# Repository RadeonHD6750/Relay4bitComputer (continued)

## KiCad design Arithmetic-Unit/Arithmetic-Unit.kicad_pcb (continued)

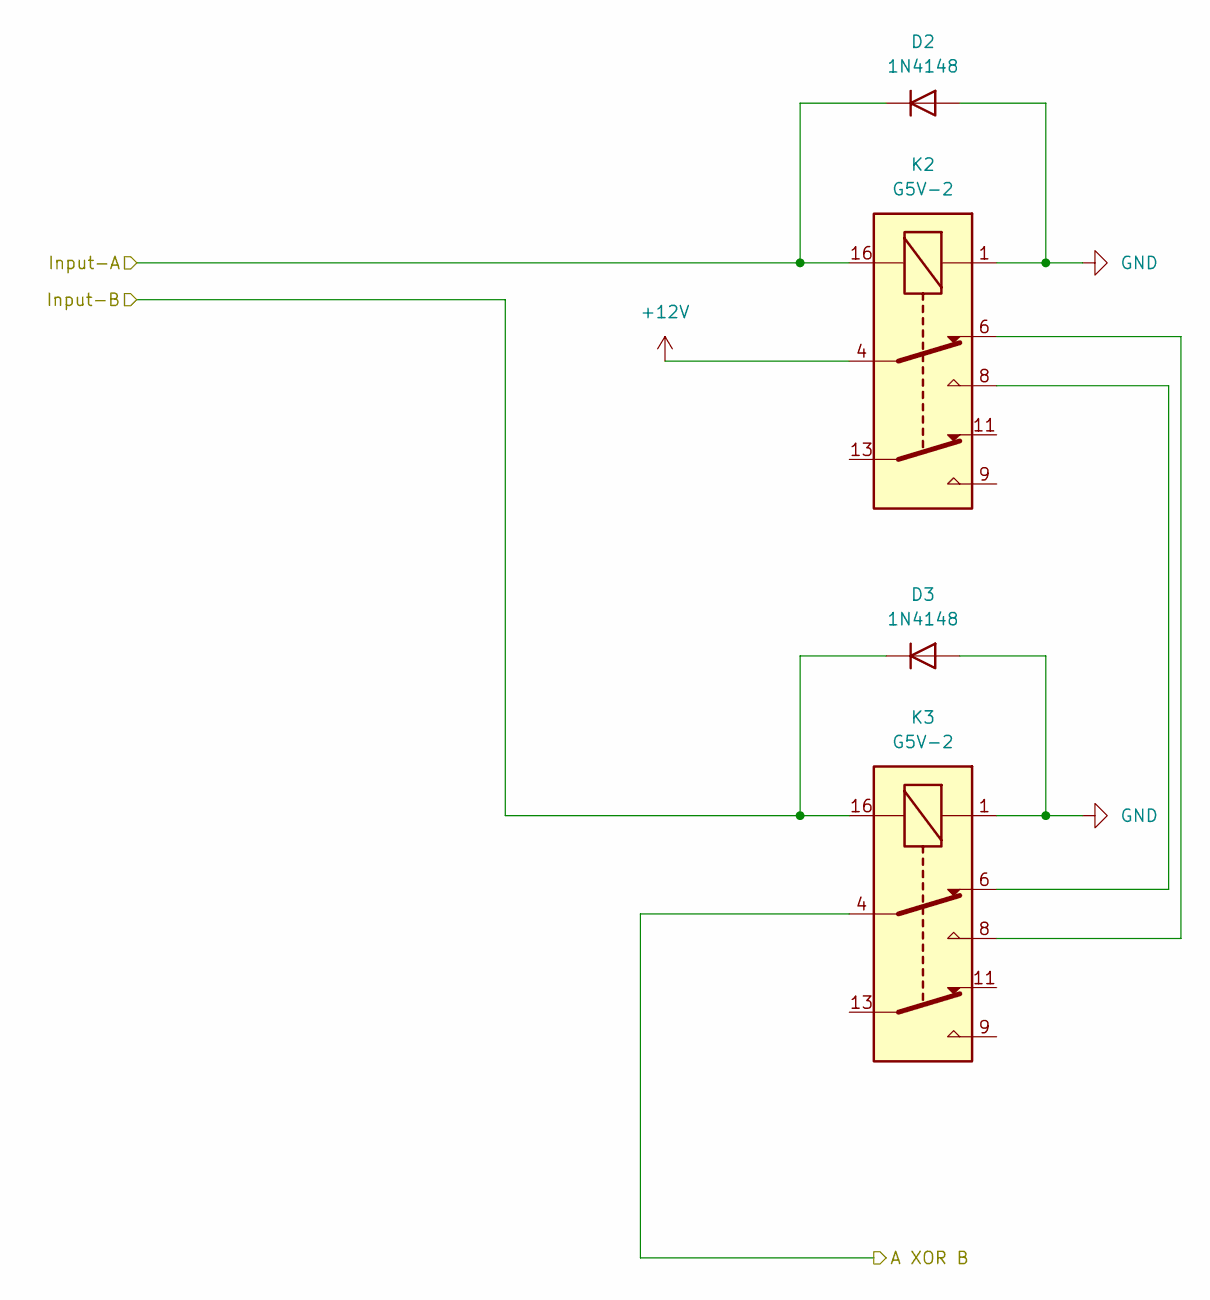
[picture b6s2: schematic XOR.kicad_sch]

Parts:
D2, D3: 1N4148; D_DO-35_SOD27_P7.62mm_Horizontal
K2, K3: G5V-2; Relay_DPDT_Omron_G5V-2

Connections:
+12V: K2.4; also elsewhere on the board
/XOR/A XOR B: K3.4; also elsewhere on the board
/XOR/Input-A: D2.1 (K), K2.16; also elsewhere on the board
/XOR/Input-B: D3.1 (K), K3.16; also elsewhere on the board
GND: D2.2 (A), D3.2 (A), K2.1, K3.1; also elsewhere on the board
unnamed: K2.6, K3.8
unnamed: K2.8, K3.6

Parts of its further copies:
D4, D5, D6, D7, D8, D9: 1N4148; D_DO-35_SOD27_P7.62mm_Horizontal
K4, K5, K6, K7, K8, K9: G5V-2; Relay_DPDT_Omron_G5V-2

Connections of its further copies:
+12V: K4.4, K6.4, K8.4; also elsewhere on the board
/XOR1/A XOR B: K5.4; also elsewhere on the board
/XOR1/Input-B: D5.1 (K), K5.16; also elsewhere on the board
/XOR2/A XOR B: K7.4; also elsewhere on the board
/XOR2/Input-B: D7.1 (K), K7.16; also elsewhere on the board
/XOR3/A XOR B: K9.4; also elsewhere on the board
/XOR3/Input-B: D9.1 (K), K9.16; also elsewhere on the board
/XOR/Input-A: D4.1 (K), D6.1 (K), D8.1 (K), K4.16, K6.16, K8.16; also elsewhere on the board
GND: D4.2 (A), D5.2 (A), D6.2 (A), D7.2 (A), D8.2 (A), D9.2 (A), K4.1, K5.1, K6.1, K7.1, K8.1, K9.1; also elsewhere on the board
unnamed: K4.6, K5.8
unnamed: K4.8, K5.6
unnamed: K6.6, K7.8
unnamed: K6.8, K7.6
unnamed: K8.6, K9.8
unnamed: K8.8, K9.6

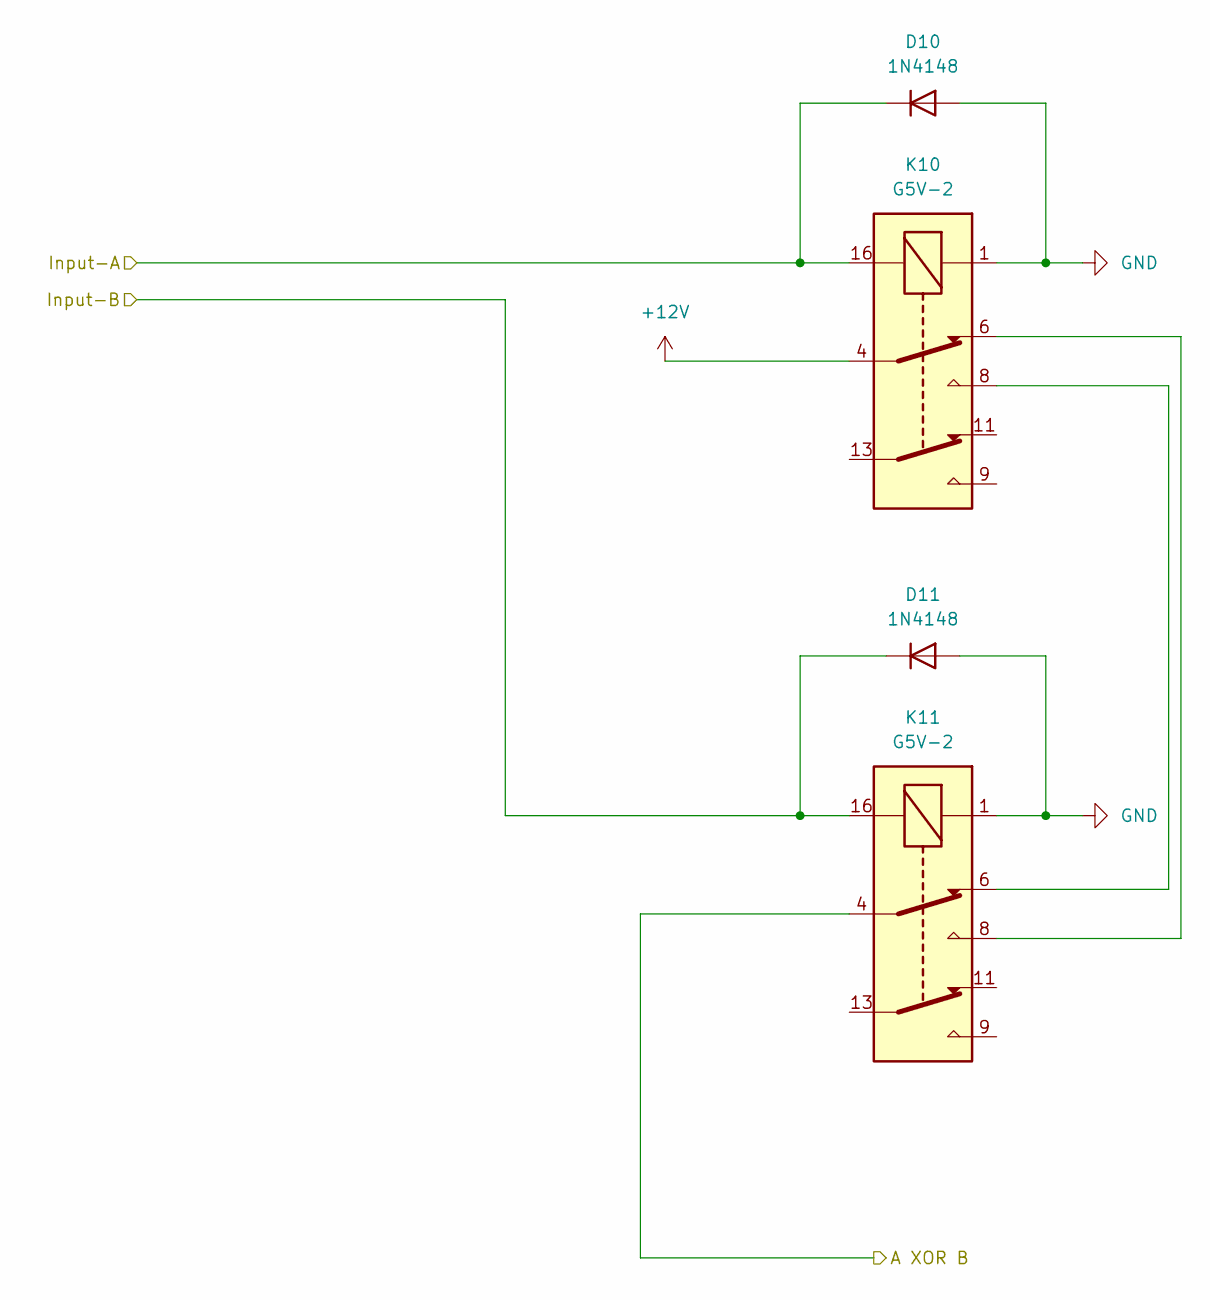
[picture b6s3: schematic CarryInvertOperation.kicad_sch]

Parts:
D10, D11: 1N4148; D_DO-35_SOD27_P7.62mm_Horizontal
K10, K11: G5V-2; Relay_DPDT_Omron_G5V-2

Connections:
+12V: K10.4; also elsewhere on the board
/CarryInvertOperation/A XOR B: K11.4; also elsewhere on the board
/CarryInvertOperation/Input-A: D10.1 (K), K10.16; also elsewhere on the board
/CarryInvertOperation/Input-B: D11.1 (K), K11.16; also elsewhere on the board
GND: D10.2 (A), D11.2 (A), K10.1, K11.1; also elsewhere on the board
unnamed: K10.6, K11.8
unnamed: K10.8, K11.6

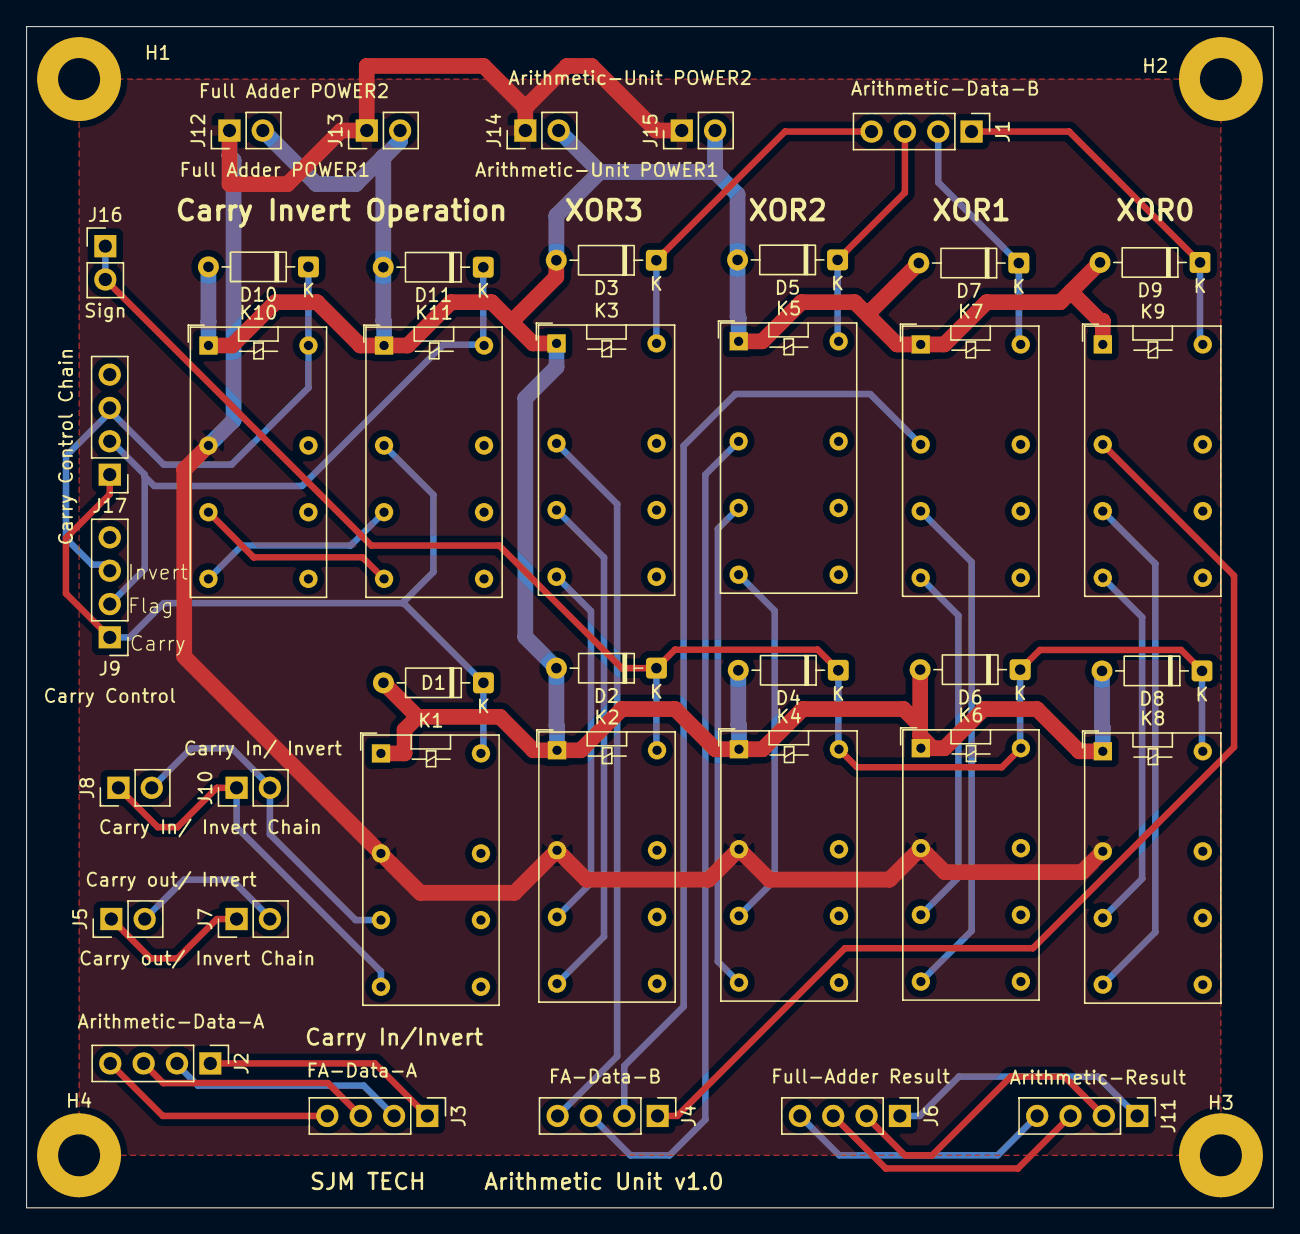
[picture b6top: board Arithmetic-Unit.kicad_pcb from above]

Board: 2 copper layers, 95.0 x 90.0 mm, 43 parts (0 on the bottom side), 36 nets.

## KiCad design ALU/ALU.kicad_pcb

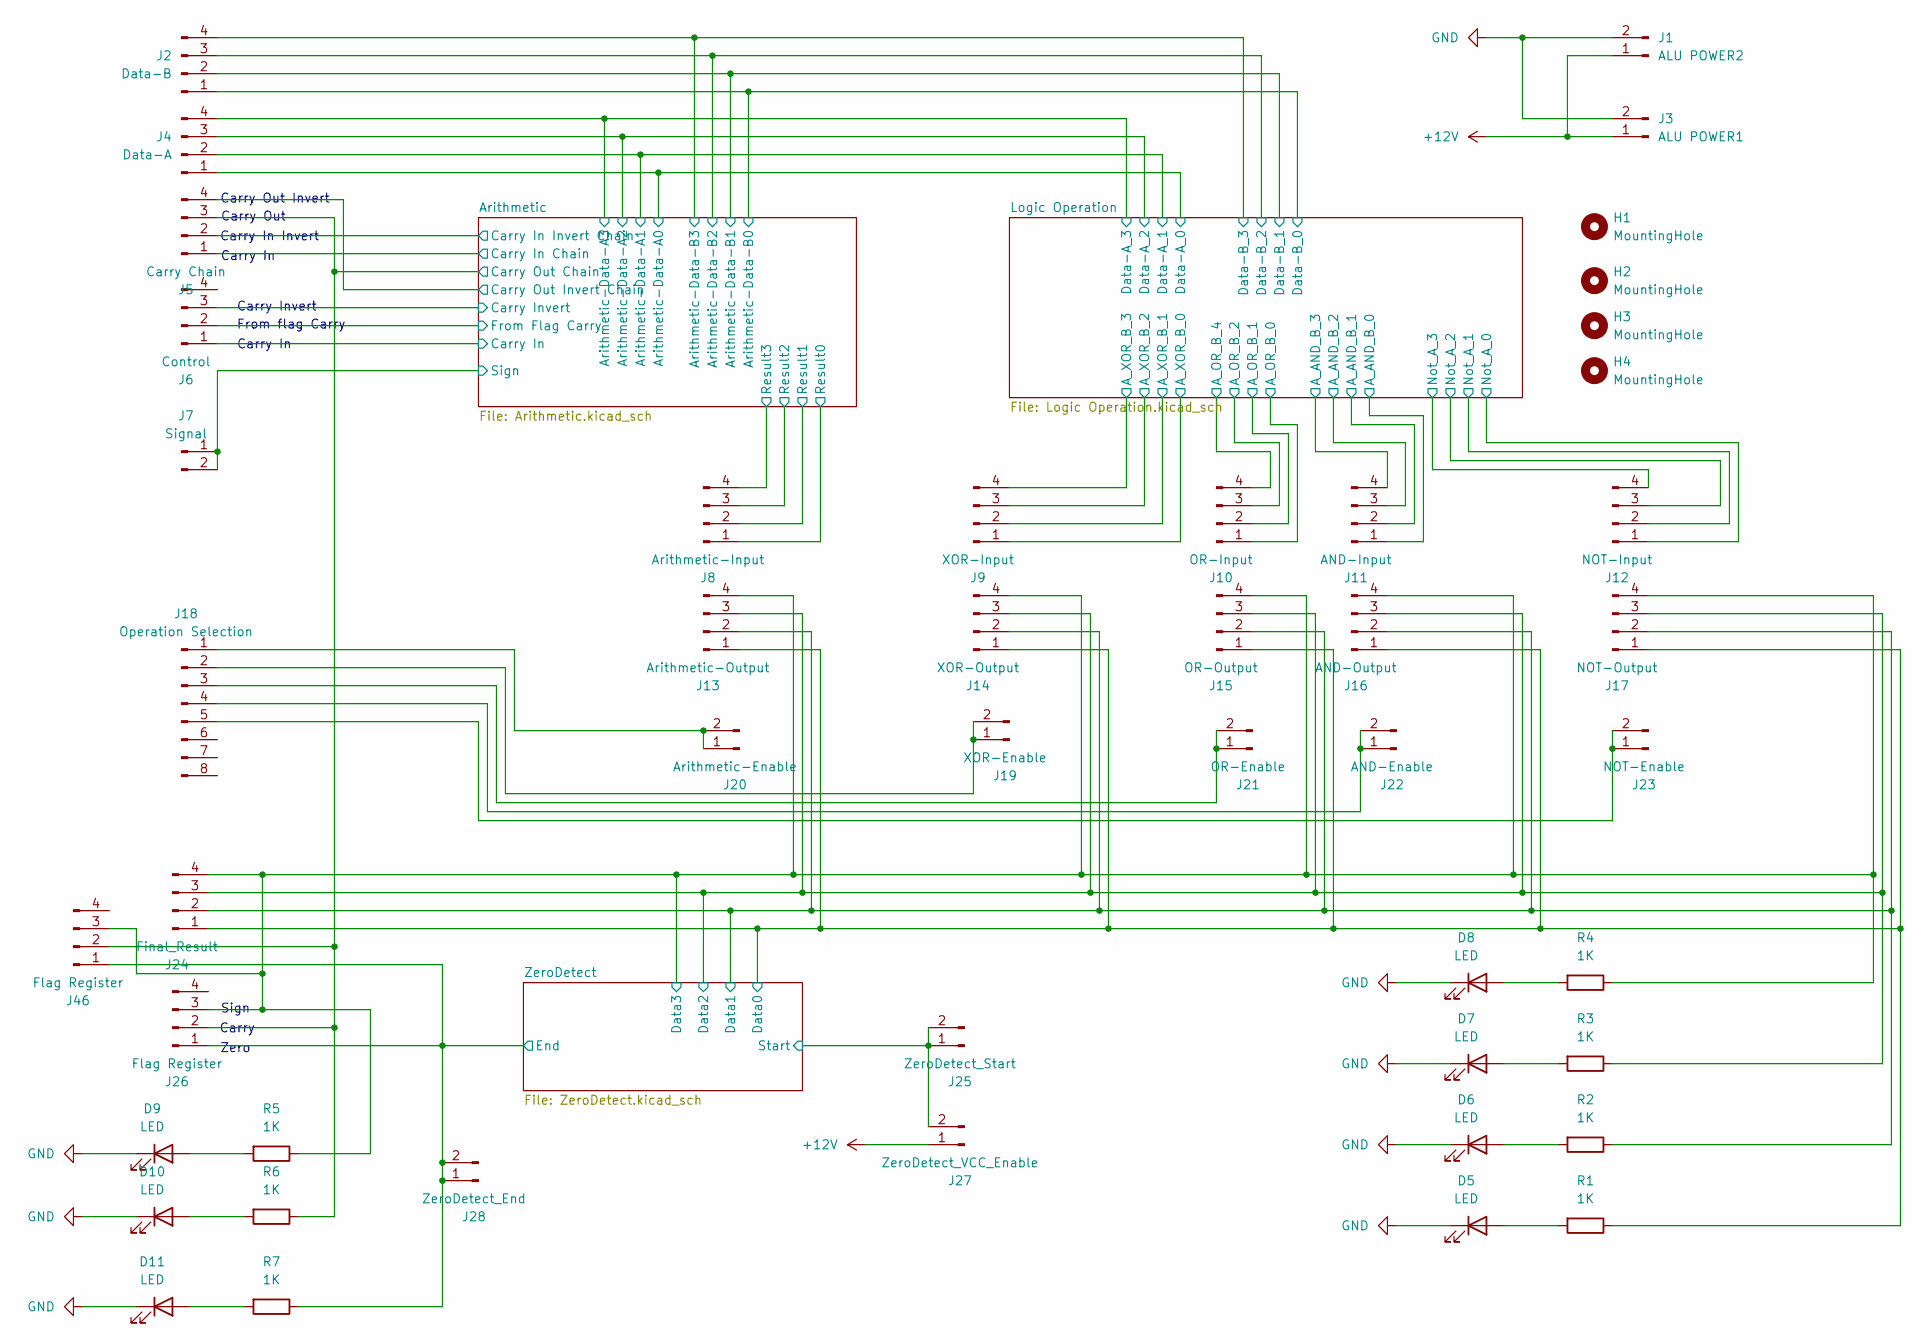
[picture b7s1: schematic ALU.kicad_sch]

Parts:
D5, D6, D7, D8, D9, D10, D11: LED; LED_D5.0mm
H1, H2, H3, H4: MountingHole; MountingHole_3.2mm_M3_Pad
J1: ALU POWER2; PinHeader_1x02_P2.54mm_Vertical
J2: Data-B; PinHeader_1x04_P2.54mm_Vertical
J3: ALU POWER1; PinHeader_1x02_P2.54mm_Vertical
J4: Data-A; PinHeader_1x04_P2.54mm_Vertical
J5: Carry Chain; PinHeader_1x04_P2.54mm_Vertical
J6: Control; PinHeader_1x04_P2.54mm_Vertical
J7: Signal; PinHeader_1x02_P2.54mm_Vertical
J8: Arithmetic-Input; PinHeader_1x04_P2.54mm_Vertical
J9: XOR-Input; PinHeader_1x04_P2.54mm_Vertical
J10: OR-Input; PinHeader_1x04_P2.54mm_Vertical
J11: AND-Input; PinHeader_1x04_P2.54mm_Vertical
J12: NOT-Input; PinHeader_1x04_P2.54mm_Vertical
J13: Arithmetic-Output; PinHeader_1x04_P2.54mm_Vertical
J14: XOR-Output; PinHeader_1x04_P2.54mm_Vertical
J15: OR-Output; PinHeader_1x04_P2.54mm_Vertical
J16: AND-Output; PinHeader_1x04_P2.54mm_Vertical
J17: NOT-Output; PinHeader_1x04_P2.54mm_Vertical
J18: Operation Selection; PinHeader_1x08_P2.54mm_Vertical
J19: XOR-Enable; PinHeader_1x02_P2.54mm_Vertical
J20: Arithmetic-Enable; PinHeader_1x02_P2.54mm_Vertical
J21: OR-Enable; PinHeader_1x02_P2.54mm_Vertical
J22: AND-Enable; PinHeader_1x02_P2.54mm_Vertical
J23: NOT-Enable; PinHeader_1x02_P2.54mm_Vertical
J24: Final_Result; PinHeader_1x04_P2.54mm_Vertical
J25: ZeroDetect_Start; PinHeader_1x02_P2.54mm_Vertical
J26, J46: Flag Register; PinHeader_1x04_P2.54mm_Vertical
J27: ZeroDetect_VCC_Enable; PinHeader_1x02_P2.54mm_Vertical
J28: ZeroDetect_End; PinHeader_1x02_P2.54mm_Vertical
R1, R2, R3, R4, R5, R6, R7: 1K; R_Axial_DIN0207_L6.3mm_D2.5mm_P10.16mm_Horizontal

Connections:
+12V: J1.1, J3.1, J27.1; also elsewhere on the board
/Arithmetic/Arithmetic-Data-A0: J4.1; also elsewhere on the board
/Arithmetic/Arithmetic-Data-A1: J4.2; also elsewhere on the board
/Arithmetic/Arithmetic-Data-A2: J4.3; also elsewhere on the board
/Arithmetic/Arithmetic-Data-A3: J4.4; also elsewhere on the board
/Arithmetic/Arithmetic-Data-B0: J2.1; also elsewhere on the board
/Arithmetic/Arithmetic-Data-B1: J2.2; also elsewhere on the board
/Arithmetic/Arithmetic-Data-B2: J2.3; also elsewhere on the board
/Arithmetic/Arithmetic-Data-B3: J2.4; also elsewhere on the board
/Arithmetic/Carry In: J6.1; also elsewhere on the board
/Arithmetic/Carry In Chain: J5.1; also elsewhere on the board
/Arithmetic/Carry In Invert Chain: J5.2; also elsewhere on the board
/Arithmetic/Carry Invert: J6.3; also elsewhere on the board
/Arithmetic/Carry Out Chain: J5.3, J26.2, J46.2, R6.1; also elsewhere on the board
/Arithmetic/Carry Out Invert Chain: J5.4; also elsewhere on the board
/Arithmetic/From Flag Carry: J6.2; also elsewhere on the board
/Arithmetic/Result0: J8.1; also elsewhere on the board
/Arithmetic/Result1: J8.2; also elsewhere on the board
/Arithmetic/Result2: J8.3; also elsewhere on the board
/Arithmetic/Result3: J8.4; also elsewhere on the board
/Arithmetic/Sign: J7.1, J7.2; also elsewhere on the board
/Logic Operation/A_AND_B_0: J11.1; also elsewhere on the board
/Logic Operation/A_AND_B_1: J11.2; also elsewhere on the board
/Logic Operation/A_AND_B_2: J11.3; also elsewhere on the board
/Logic Operation/A_AND_B_3: J11.4; also elsewhere on the board
/Logic Operation/A_OR_B_0: J10.1; also elsewhere on the board
/Logic Operation/A_OR_B_1: J10.2; also elsewhere on the board
/Logic Operation/A_OR_B_2: J10.3; also elsewhere on the board
/Logic Operation/A_OR_B_4: J10.4; also elsewhere on the board
/Logic Operation/A_XOR_B_0: J9.1; also elsewhere on the board
/Logic Operation/A_XOR_B_1: J9.2; also elsewhere on the board
/Logic Operation/A_XOR_B_2: J9.3; also elsewhere on the board
/Logic Operation/A_XOR_B_3: J9.4; also elsewhere on the board
/Logic Operation/Not_A_0: J12.1; also elsewhere on the board
/Logic Operation/Not_A_1: J12.2; also elsewhere on the board
/Logic Operation/Not_A_2: J12.3; also elsewhere on the board
/Logic Operation/Not_A_3: J12.4; also elsewhere on the board
/ZeroDetect/Data0: J13.1, J14.1, J15.1, J16.1, J17.1, J24.1, R1.1; also elsewhere on the board
/ZeroDetect/Data1: J13.2, J14.2, J15.2, J16.2, J17.2, J24.2, R2.1; also elsewhere on the board
/ZeroDetect/Data2: J13.3, J14.3, J15.3, J16.3, J17.3, J24.3, R3.1; also elsewhere on the board
/ZeroDetect/Data3: J13.4, J14.4, J15.4, J16.4, J17.4, J24.4, J26.3, J46.3, R4.1, R5.1; also elsewhere on the board
/ZeroDetect/End: J26.1, J28.1, J28.2, J46.1, R7.1; also elsewhere on the board
/ZeroDetect/Start: J25.1, J25.2, J27.2; also elsewhere on the board
GND: D5.1 (K), D6.1 (K), D7.1 (K), D8.1 (K), D9.1 (K), D10.1 (K), D11.1 (K), J1.2, J3.2; also elsewhere on the board
unnamed: D5.2 (A), R1.2
unnamed: D6.2 (A), R2.2
unnamed: D7.2 (A), R3.2
unnamed: D8.2 (A), R4.2
unnamed: D9.2 (A), R5.2
unnamed: D10.2 (A), R6.2
unnamed: D11.2 (A), R7.2
unnamed: J18.1, J20.1, J20.2
unnamed: J18.2, J19.1, J19.2
unnamed: J18.3, J21.1, J21.2
unnamed: J18.4, J22.1, J22.2
unnamed: J18.5, J23.1, J23.2

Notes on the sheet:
Carry In
Sign
Carry
From flag Carry
Carry In Invert
Zero
Carry Out
Carry Out Invert
Carry Invert

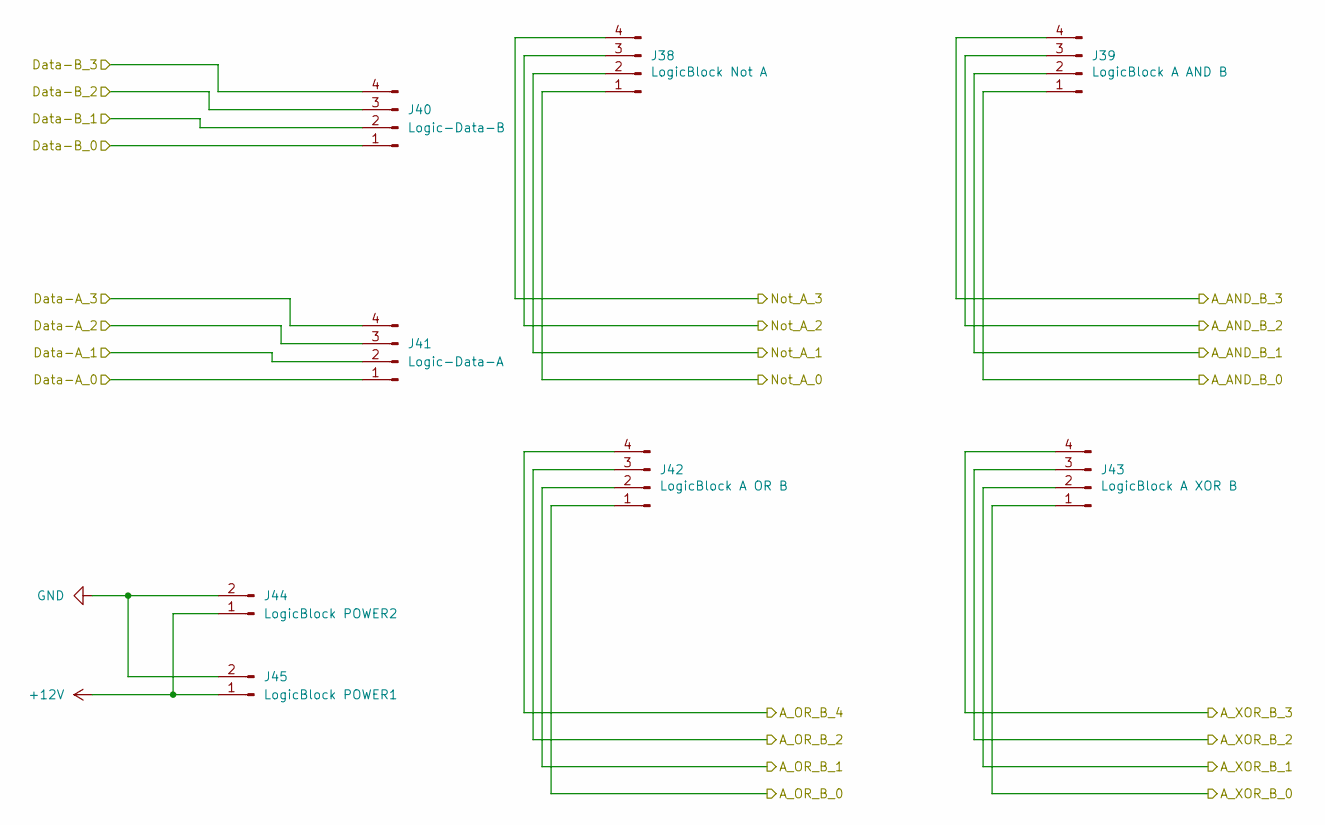
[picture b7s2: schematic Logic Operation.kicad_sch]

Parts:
J38: LogicBlock Not A; PinHeader_1x04_P2.54mm_Vertical
J39: LogicBlock A AND B; PinHeader_1x04_P2.54mm_Vertical
J40: Logic-Data-B; PinHeader_1x04_P2.54mm_Vertical
J41: Logic-Data-A; PinHeader_1x04_P2.54mm_Vertical
J42: LogicBlock A OR B; PinHeader_1x04_P2.54mm_Vertical
J43: LogicBlock A XOR B; PinHeader_1x04_P2.54mm_Vertical
J44: LogicBlock POWER2; PinHeader_1x02_P2.54mm_Vertical
J45: LogicBlock POWER1; PinHeader_1x02_P2.54mm_Vertical

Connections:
+12V: J44.1, J45.1; also elsewhere on the board
/Arithmetic/Arithmetic-Data-A0: J41.1; also elsewhere on the board
/Arithmetic/Arithmetic-Data-A1: J41.2; also elsewhere on the board
/Arithmetic/Arithmetic-Data-A2: J41.3; also elsewhere on the board
/Arithmetic/Arithmetic-Data-A3: J41.4; also elsewhere on the board
/Arithmetic/Arithmetic-Data-B0: J40.1; also elsewhere on the board
/Arithmetic/Arithmetic-Data-B1: J40.2; also elsewhere on the board
/Arithmetic/Arithmetic-Data-B2: J40.3; also elsewhere on the board
/Arithmetic/Arithmetic-Data-B3: J40.4; also elsewhere on the board
/Logic Operation/A_AND_B_0: J39.1; also elsewhere on the board
/Logic Operation/A_AND_B_1: J39.2; also elsewhere on the board
/Logic Operation/A_AND_B_2: J39.3; also elsewhere on the board
/Logic Operation/A_AND_B_3: J39.4; also elsewhere on the board
/Logic Operation/A_OR_B_0: J42.1; also elsewhere on the board
/Logic Operation/A_OR_B_1: J42.2; also elsewhere on the board
/Logic Operation/A_OR_B_2: J42.3; also elsewhere on the board
/Logic Operation/A_OR_B_4: J42.4; also elsewhere on the board
/Logic Operation/A_XOR_B_0: J43.1; also elsewhere on the board
/Logic Operation/A_XOR_B_1: J43.2; also elsewhere on the board
/Logic Operation/A_XOR_B_2: J43.3; also elsewhere on the board
/Logic Operation/A_XOR_B_3: J43.4; also elsewhere on the board
/Logic Operation/Not_A_0: J38.1; also elsewhere on the board
/Logic Operation/Not_A_1: J38.2; also elsewhere on the board
/Logic Operation/Not_A_2: J38.3; also elsewhere on the board
/Logic Operation/Not_A_3: J38.4; also elsewhere on the board
GND: J44.2, J45.2; also elsewhere on the board

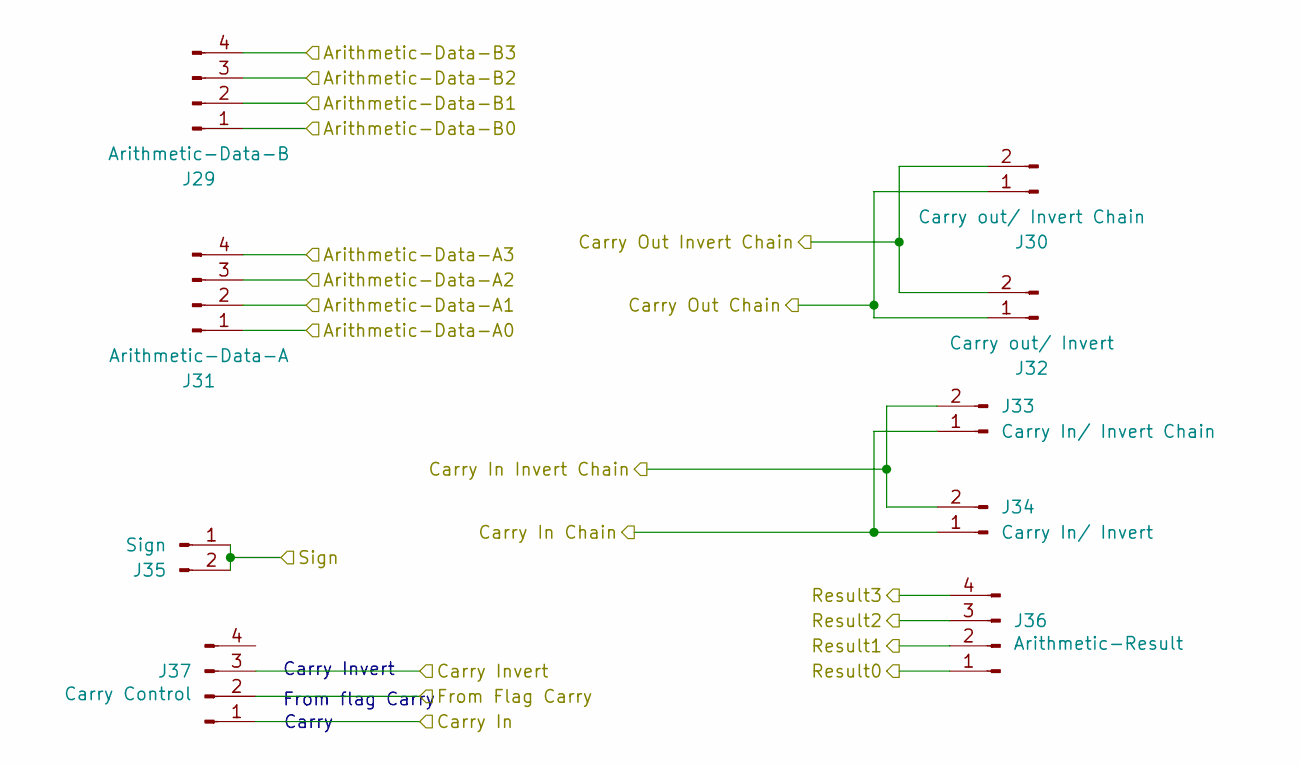
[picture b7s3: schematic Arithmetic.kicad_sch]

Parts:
J29: Arithmetic-Data-B; PinHeader_1x04_P2.54mm_Vertical
J30: Carry out/ Invert Chain; PinHeader_1x02_P2.54mm_Vertical
J31: Arithmetic-Data-A; PinHeader_1x04_P2.54mm_Vertical
J32: Carry out/ Invert; PinHeader_1x02_P2.54mm_Vertical
J33: Carry In/ Invert Chain; PinHeader_1x02_P2.54mm_Vertical
J34: Carry In/ Invert; PinHeader_1x02_P2.54mm_Vertical
J35: Sign; PinHeader_1x02_P2.54mm_Vertical
J36: Arithmetic-Result; PinHeader_1x04_P2.54mm_Vertical
J37: Carry Control; PinHeader_1x04_P2.54mm_Vertical

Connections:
/Arithmetic/Arithmetic-Data-A0: J31.1; also elsewhere on the board
/Arithmetic/Arithmetic-Data-A1: J31.2; also elsewhere on the board
/Arithmetic/Arithmetic-Data-A2: J31.3; also elsewhere on the board
/Arithmetic/Arithmetic-Data-A3: J31.4; also elsewhere on the board
/Arithmetic/Arithmetic-Data-B0: J29.1; also elsewhere on the board
/Arithmetic/Arithmetic-Data-B1: J29.2; also elsewhere on the board
/Arithmetic/Arithmetic-Data-B2: J29.3; also elsewhere on the board
/Arithmetic/Arithmetic-Data-B3: J29.4; also elsewhere on the board
/Arithmetic/Carry In: J37.1; also elsewhere on the board
/Arithmetic/Carry In Chain: J33.1, J34.1; also elsewhere on the board
/Arithmetic/Carry In Invert Chain: J33.2, J34.2; also elsewhere on the board
/Arithmetic/Carry Invert: J37.3; also elsewhere on the board
/Arithmetic/Carry Out Chain: J30.1, J32.1; also elsewhere on the board
/Arithmetic/Carry Out Invert Chain: J30.2, J32.2; also elsewhere on the board
/Arithmetic/From Flag Carry: J37.2; also elsewhere on the board
/Arithmetic/Result0: J36.1; also elsewhere on the board
/Arithmetic/Result1: J36.2; also elsewhere on the board
/Arithmetic/Result2: J36.3; also elsewhere on the board
/Arithmetic/Result3: J36.4; also elsewhere on the board
/Arithmetic/Sign: J35.1, J35.2; also elsewhere on the board

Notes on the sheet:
Carry
From flag Carry
Carry Invert

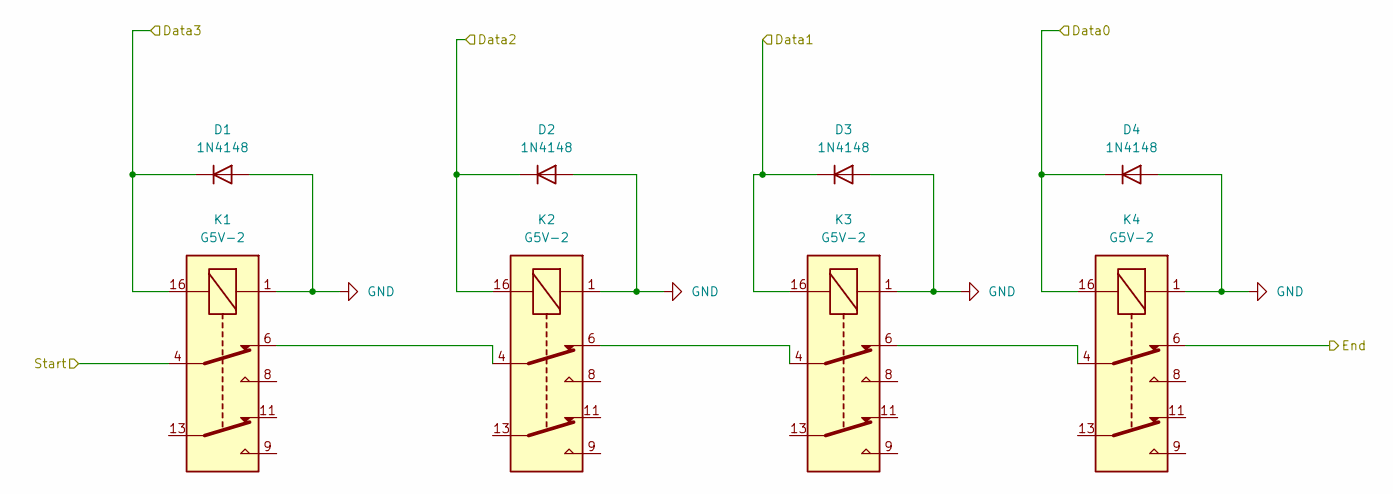
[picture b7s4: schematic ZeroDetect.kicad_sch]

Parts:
D1, D2, D3, D4: 1N4148; D_DO-35_SOD27_P7.62mm_Horizontal
K1, K2, K3, K4: G5V-2; Relay_DPDT_Omron_G5V-2

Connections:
/ZeroDetect/Data0: D4.1 (K), K4.16; also elsewhere on the board
/ZeroDetect/Data1: D3.1 (K), K3.16; also elsewhere on the board
/ZeroDetect/Data2: D2.1 (K), K2.16; also elsewhere on the board
/ZeroDetect/Data3: D1.1 (K), K1.16; also elsewhere on the board
/ZeroDetect/End: K4.6; also elsewhere on the board
/ZeroDetect/Start: K1.4; also elsewhere on the board
GND: D1.2 (A), D2.2 (A), D3.2 (A), D4.2 (A), K1.1, K2.1, K3.1, K4.1; also elsewhere on the board
unnamed: K1.6, K2.4
unnamed: K2.6, K3.4
unnamed: K3.6, K4.4

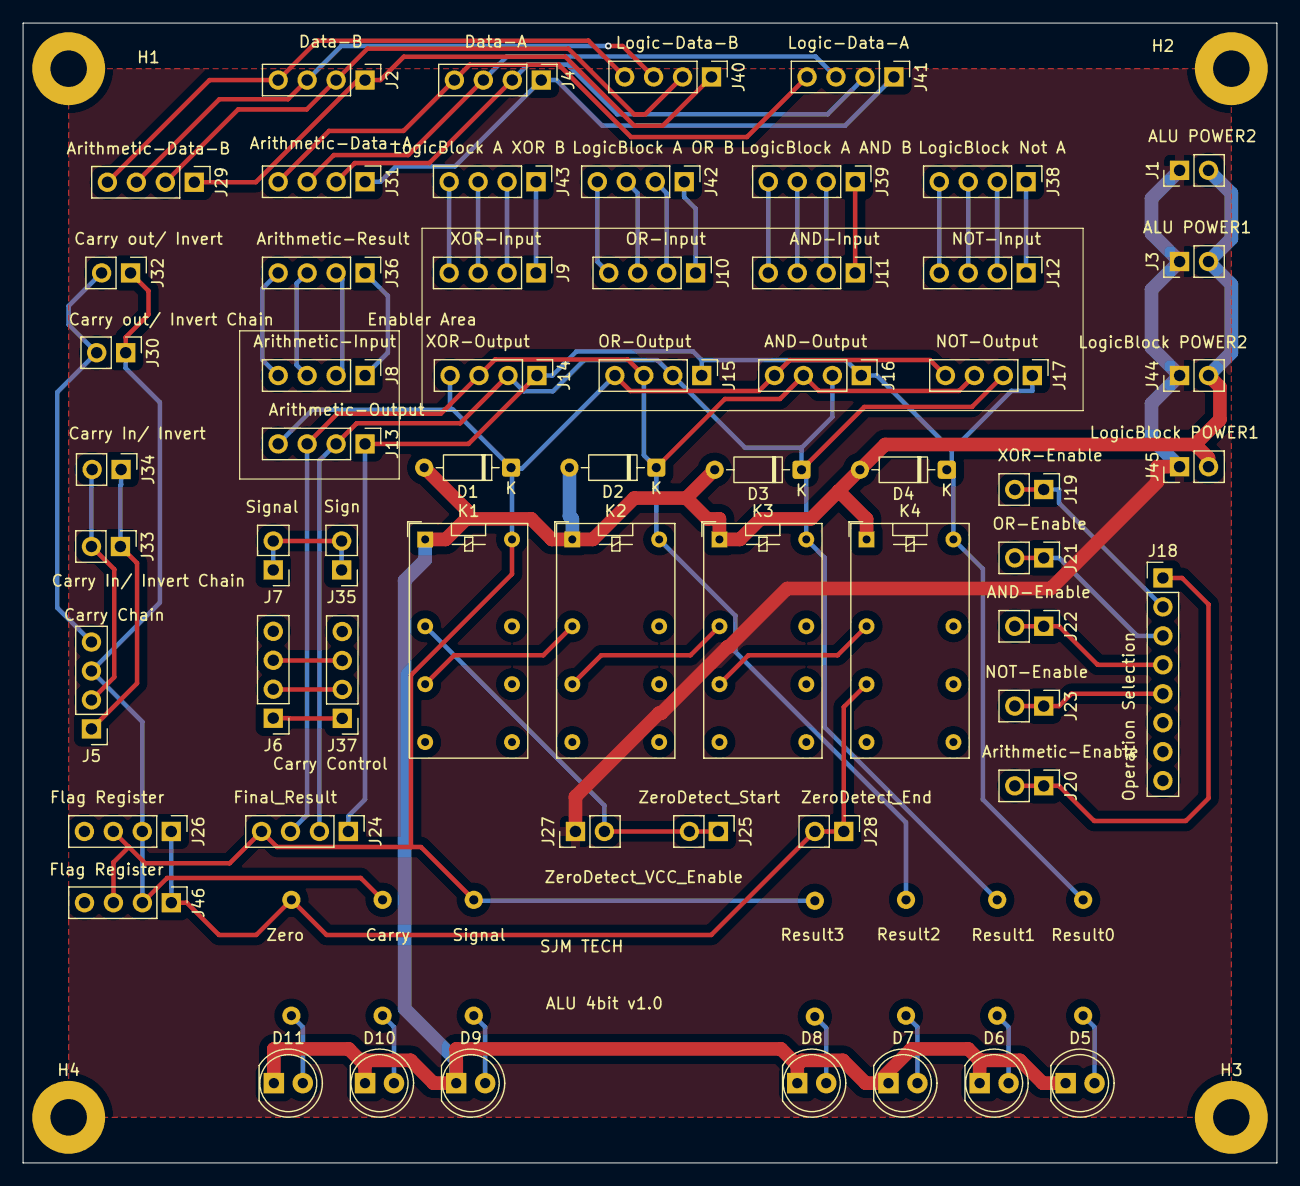
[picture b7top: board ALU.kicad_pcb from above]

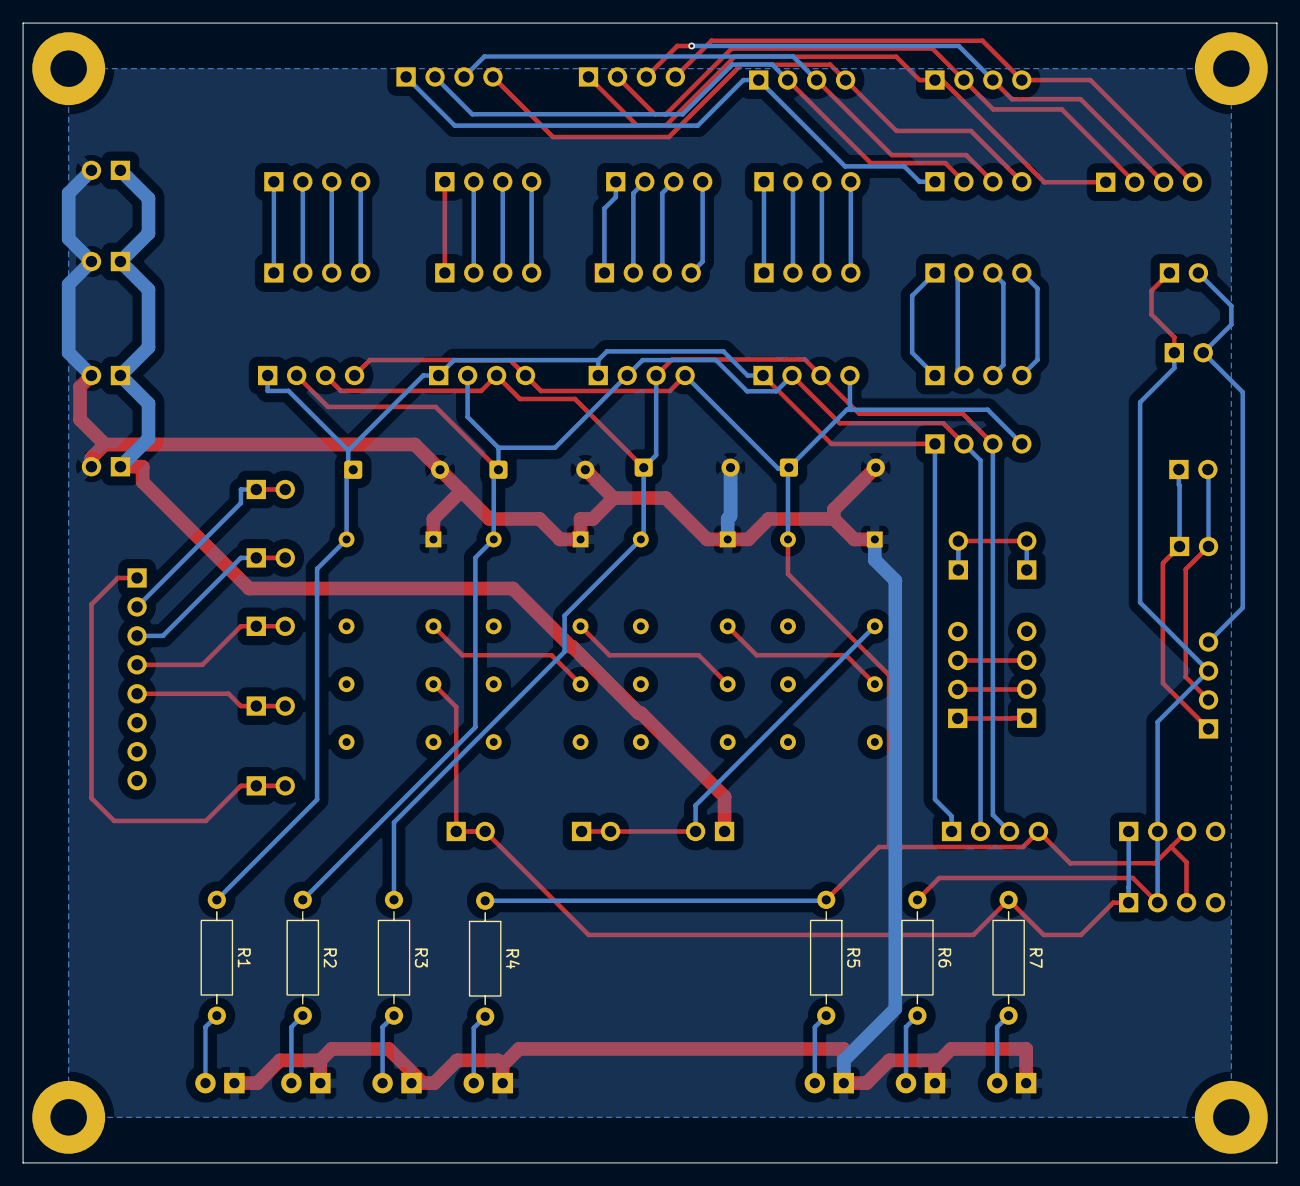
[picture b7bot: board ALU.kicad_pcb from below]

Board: 2 copper layers, 110.0 x 100.0 mm, 72 parts (7 on the bottom side), 59 nets.
